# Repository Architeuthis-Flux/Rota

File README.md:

# Rǒta
Here are some different Rǒtas with different options

That flashing means it wants your input. These decimal points do way more work than regular decimal points, they tell you a lot about what's going on. When you don't have segments to make crude letters and stuff, you need to get creative with dots.

https://user-images.githubusercontent.com/20519442/197625332-2014cbfb-5107-4166-b01f-a8d20bc4a214.mp4

Rǒta is a tool for counting things while being all nerdily extra about it. Are there more efficient ways to count things? Yes. But will those things increase your exposure to Nixie tubes and rotary dials? No? Well then if that's what passes for progress nowadays then I'm going to go live on a mountain somewhere and count things the cooler way, with nixie tubes.

It was originally conceived as a gift for a duck hunting lodge, but now I'm making a few more and I know not everyone is into hunting so it's been generalized into a tool for just counting stuff in general where those $3 hand clickers or a golf pencil just lacks the glamour you need in your life. 

Instead of using sequences of numbers to use the special functions, now you just dial 0 and then the function you want which is printed on the number plate. 

here's the special function menu map
```
note - I'm calling moving the dial just a little to turn the display on a "click"
when inside a special function, dial anything to exit (preferably 0 because it's only reading intermittently when in menus, so it's most likely to register)

0 -- enter/exit menu or function   shows 111 when you're in the menu)
1 -- stopwatch                    click to start, click again to see last time.
2 -- show battery voltage         briefly turns off the display to get a more accurate reading (not under load)
3 -- new day                      this stores the total since the last time you started a new day. maximum 63 days
4 -- does nothing
5 -- enter a count by digits      enter 3 digits (hundreds - tens - ones) to add to your daily total
6 -- show history                 click through each day with first the day number (on the left) then the total for that day
7 -- toggle day/total display     either shows the count for that day or the running total of all days (default is total)
8 -- golf mode                    keep score for golf - first enter 1-4 players and the decimal points show which player's turn it is
9 -- clear everything             dial 9 again to confirm. dial anything else to go back
999999 -- emergency clear         dial 9 six times to emergency clear everything in case something gets messed up same as dialing 10 9 9
                                  you can also short the middle pulse pin high for super duper emergency clear

```

The voltage display was added because I was having issues with the K155ID1s browning out before the HV module (it still blows my mind that it works down to like 3V), so the display would just show all the digits on because the nixie drivers weren't blocking any current. 

So now I added a HV shutdown and a super simple voltage sense divider that drops the 9 down by half so it can be read by the AVR64DD32's ADC.

Now if the battery voltage is too low, it shuts down the display but still takes input. In case you don't have a spare battery but still want to count. And the power draw is so low for just the microcontroller that the battery life might as well be infinite.

https://user-images.githubusercontent.com/20519442/197626419-59003e0c-a97b-495f-a466-c8ea541df162.mp4

If you notice in the video, the display flashes when the battery voltage updates, that's because when it does the measurement, it briefly shuts the HV module down so we can measure the battery voltage unloaded. Because this thing draws ~300-400mA when it's on so without doing a ton of math and testing different 9v batteries to correct for it, the voltage it shows would be like ~2V lower than it really is unloaded. 

I probably should have put in a fresher battery before I filmed this. 

I also had to design a case for this because I'd always get anxious watching other people use it without one. People with smaller hands tend to put their fingers right on the high voltage section on the back of the Nixies. 

This project really helped me change my lukewarm feelings towards rapid prototyping, I've had a 3D printer for years but never really used it much. I found out the reason it never worked is the original spool of filament Sindoh included was garbage. So my prints would always turn into an absolute mess of spaghetti. I finally bought a fresh spool of filament and it works great now.

I'll definitely have the case made by someone with a more expensive printer when I sell these or give them away, but to get the fit right and make sure there's room for everything inside, 3D printing really saved the day here.

Putting in the number plate (which I just found out the name of) on these old dials really makes you appreciate how much thought they put into things in the 60's. Like on most phones you would only do this once, but they came up with a really cool system for it.

How you do it is by sticking a screwdriver under the ring at the 6 and moving a lever down to the 8 position to release the middle thing.

With it off you can see what's going on 

Then you just twist this pressure plate and it comes off. 

This isn't the final number plate from above because I'm a millennial and don't have a regular 2D printer. But I might try it on a plotter or a silkscreen to get a nicer finish.

I had to move the holes a bit to get it to line up with the dial, I must have carelessly moved the holes on the Edge Cuts layer in Kicad, but the new Kicad files on here are fixed (as well as a couple other problems) if you want to have these boards made yourself. 

Yes I cleaned that flux off. For Nixies it's particularly important because flux lets enough current flow at that voltage to cause ghosting. I had a lot of problems wit ghosting on the first digit and I tried a bunch of things to get rid of it, eventually what fixed it for me was putting a 220KΩ resistor between high voltage and ground to both drop the voltage a bit (these tiny HV modules don't have an adjustment knob like the bigger ones) and bleed off the extra charge you get when you do low-side switching on nixies.

PCBway was nice enough to sponsor this project. I had never used them before but the boards they sent were great. And their matte black finish is really velvety. 

It really seems like they spend a good deal of time with a human looking at your boards and making sure there aren't any problems. And I usually do a lot of weird stuff with my boards that falls outside of the usual best practices of PCB design. But they seemed to roll with it pretty well and make sure I did it on purpose (that came up a lot more with breadWare which they also sponsored.) Which is crazy to me because of how cheap the service is. You'd think it wouldn't be worth their time for my ~$20. 

Either way, I was ready to just pay them for my boards if they were shitty and say so here. But that wasn't necessary because they really did a great job on these. 

# RotaDuck (this is the previous revision so I'm leaving this here)
Sticking Nixie tubes to an old rotary telephone dial

Here's a video of it in action

https://user-images.githubusercontent.com/20519442/176002505-34b7ac66-cf38-471d-8984-42ffa85f04d7.mp4

And there's a few more on my [Youtube channel](https://www.youtube.com/user/arabidsquid/videos)

I'll do a more complete write-up at some point in the future, but for now I'll mention a few things.

It stores the running count (and a history of recent entries) in EEPROM because when the dial returns to it's resting position, the power is completely cut off. That makes it so I couldn't just use timing to figure out when the pulses stop (and the number that was ultimately dialed) so instead I put in a resistor ladder so the between the 3 contacts on the dial to give me 1/2 voltage on the last number, when the dial is between 0 and the end. that gives me a waveform like this:
```
   _   _   _   _
__| |_| |_| |_| |_,-,___
```
So it does all the saving during that shorter last pulse, which is pretty tight because EEPROM access is relatively slow. 

I didn't want to add any buttons to it so instead it uses multiple 9s and 0s for special codes, here's the list of what they do
```
0   - subtract the next number dialed from the total
000 - clear all counts to 0

9   - show total for all days
99  - list each day and the total for each
999 - start a new day
```
Here's what I'm talking about when I say days. So this was originally designed for duck hunting (hence the duck in the name) as a gift for a duck hunting club. If you want to count how many ducks you got, we'd usually bring one of those mechanical clicker counters and just keep a running total.But I figured if I'm making a thing to count how many ducks were shot during a trip, it might also be useful to have that information separated by days if you want to keep a separate daily and running total. 

At some point I'll print that menu in the middle of the dial.

If you intend to make one of these for yourself, you should probably know this thing is like 90% bodges and perfboard circuits. I eyeballed the shape of the dial cutout nearly perfect, except that it's flipped on the board. So instead of just redoing the board like a sane person, I just mounted it with everything on the wrong side and bodged wired a ton of things to make it work. That's why there are those arrays in the code to convert the number shown to the number its actually wired to. So if you really want one, let me know and I can do a version 2 that will be 100x easier to put together. 

I also made a rechargeable one by dead bug soldering a tiny 10DFN MCP73213T charge controller and putting in 2 1/2 AA sized lithium batteries, but after using it a while, the simplicity of just using a 9 volt battery is much nicer (and lasts a lot longer.)

Eventually that red wire sticking out will be connected to a barrel jack port. Once I decide on an enclosure.

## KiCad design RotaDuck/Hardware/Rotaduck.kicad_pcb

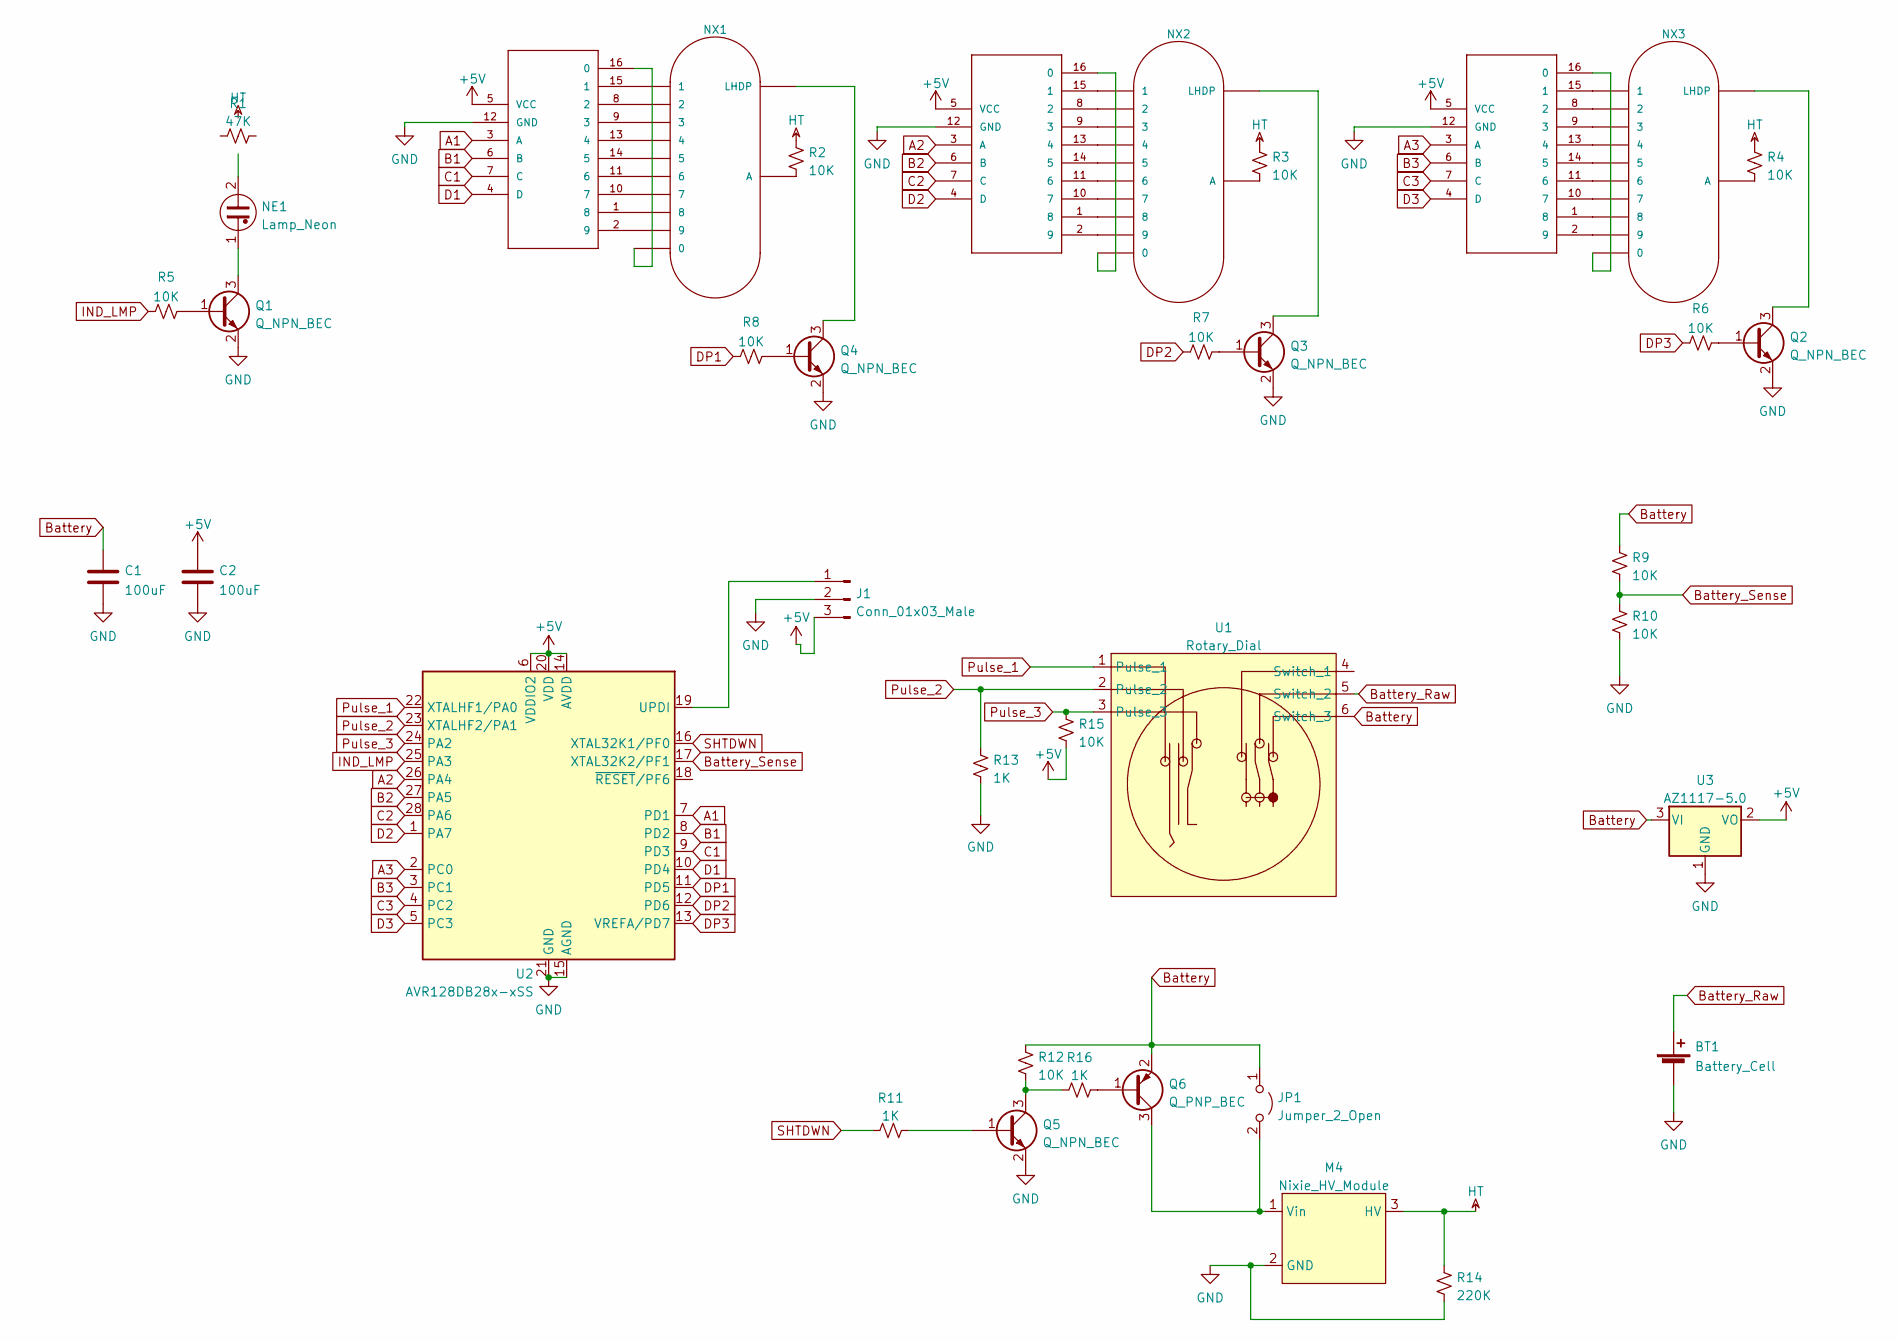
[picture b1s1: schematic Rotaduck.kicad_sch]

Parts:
BT1: Battery_Cell; PinHeader_1x02_P2.54mm_Vertical
C1, C2: 100uF; C_1206_3216Metric_Pad1.33x1.80mm_HandSolder
J1: Conn_01x03_Male; PinHeader_1x03_P2.54mm_Vertical
JP1: Jumper_2_Open; SolderJumper-2_P1.3mm_Open_RoundedPad1.0x1.5mm
M1, M2, M3: 74141DIP16; DIP-16_W7.62mm
M4: Nixie_HV_Module; Nixie_HV_Module_Small
NE1: Lamp_Neon; PinHeader_1x02_P2.54mm_Vertical
NX1, NX2, NX3: IN-12BNOHOLE; nixies-us-IN-12-DSUB
Q1, Q2, Q3, Q4, Q5: Q_NPN_BEC; SOT-23
Q6: Q_PNP_BEC; SOT-23
R1: 47K; R_1206_3216Metric_Pad1.30x1.75mm_HandSolder
R2, R3, R4: 10K; R_1206_3216Metric_Pad1.30x1.75mm_HandSolder
R5, R6, R7, R8, R9, R10, R12, R15: 10K; R_0805_2012Metric_Pad1.20x1.40mm_HandSolder
R11, R13, R16: 1K; R_0805_2012Metric_Pad1.20x1.40mm_HandSolder
R14: 220K; R_1206_3216Metric_Pad1.30x1.75mm_HandSolder
U1: Rotary_Dial; PinHeader_1x06_P2.54mm_Vertical
U2: AVR128DB28x-xSS; SSOP-28_5.3x10.2mm_P0.65mm
U3: AZ1117-5.0; SOT-223-3_TabPin2

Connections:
+5V: C2.1, J1.3, M1.5 (VCC), M2.5 (VCC), M3.5 (VCC), R15.2, U2.6 (VDDIO2), U2.14 (AVDD), U2.18 (~RESET/PF6), U2.20 (VDD), U3.2 (VO)
A1: M1.3 (A), U2.7 (PD1)
A2: M2.3 (A), U2.26 (PA4)
A3: M3.3 (A), U2.2 (PC0)
B1: M1.6 (B), U2.8 (PD2)
B2: M2.6 (B), U2.27 (PA5)
B3: M3.6 (B), U2.3 (PC1)
Battery: C1.1, JP1.1 (A), Q6.2 (E), R9.2, R12.1, U1.6 (Switch_3), U3.3 (VI)
Battery_Raw: BT1.1 (+), U1.5 (Switch_2)
Battery_Sense: R9.1, R10.2, U2.17 (XTAL32K2/PF1)
C1: M1.7 (C), U2.9 (PD3)
C2: M2.7 (C), U2.28 (PA6)
C3: M3.7 (C), U2.4 (PC2)
D1: M1.4 (D), U2.10 (PD4)
D2: M2.4 (D), U2.1 (PA7)
D3: M3.4 (D), U2.5 (PC3)
DP1: R8.2, U2.11 (PD5)
DP2: R7.2, U2.12 (PD6)
DP3: R6.2, U2.13 (VREFA/PD7)
GND: BT1.2 (-), C1.2, C2.2, J1.2, M1.12 (GND), M2.12 (GND), M3.12 (GND), M4.2 (GND), Q1.2 (E), Q2.2 (E), Q3.2 (E), Q4.2 (E), Q5.2 (E), R10.1, R13.2, R14.2, U2.15 (AGND), U2.21 (GND), U3.1 (GND)
HT: M4.3 (HV), R1.2, R2.2, R3.2, R4.2, R14.1
IND_LMP: R5.2, U2.25 (PA3)
unnamed: J1.1, U2.19 (UPDI)
unnamed: JP1.2 (B), M4.1 (Vin), Q6.3 (C)
unnamed: M1.1 (8), NX1.8
unnamed: M1.2 (9), NX1.9
unnamed: M1.8 (2), NX1.2
unnamed: M1.9 (3), NX1.3
unnamed: M1.10 (7), NX1.7
unnamed: M1.11 (6), NX1.6
unnamed: M1.13 (4), NX1.4
unnamed: M1.14 (5), NX1.5
unnamed: M1.15 (1), NX1.1
unnamed: M1.16 (0), NX1.0
unnamed: M2.1 (8), NX2.8
unnamed: M2.2 (9), NX2.9
unnamed: M2.8 (2), NX2.2
unnamed: M2.9 (3), NX2.3
unnamed: M2.10 (7), NX2.7
unnamed: M2.11 (6), NX2.6
unnamed: M2.13 (4), NX2.4
unnamed: M2.14 (5), NX2.5
unnamed: M2.15 (1), NX2.1
unnamed: M2.16 (0), NX2.0
unnamed: M3.1 (8), NX3.8
unnamed: M3.2 (9), NX3.9
unnamed: M3.8 (2), NX3.2
unnamed: M3.9 (3), NX3.3
unnamed: M3.10 (7), NX3.7
unnamed: M3.11 (6), NX3.6
unnamed: M3.13 (4), NX3.4
unnamed: M3.14 (5), NX3.5
unnamed: M3.15 (1), NX3.1
unnamed: M3.16 (0), NX3.0
unnamed: NE1.1, Q1.3 (C)
unnamed: NE1.2, R1.1
unnamed: NX1.A, R2.1
unnamed: NX1.LHDP, Q4.3 (C)
unnamed: NX2.A, R3.1
unnamed: NX2.LHDP, Q3.3 (C)
unnamed: NX3.A, R4.1
unnamed: NX3.LHDP, Q2.3 (C)
unnamed: Q1.1 (B), R5.1
unnamed: Q2.1 (B), R6.1
unnamed: Q3.1 (B), R7.1
unnamed: Q4.1 (B), R8.1
unnamed: Q5.3 (C), R12.2, R16.1
unnamed: Q5.1 (B), R11.1
unnamed: Q6.1 (B), R16.2
Pulse_1: U1.1 (Pulse_1), U2.22 (XTALHF1/PA0)
Pulse_2: R13.1, U1.2 (Pulse_2), U2.23 (XTALHF2/PA1)
Pulse_3: R15.1, U1.3 (Pulse_3), U2.24 (PA2)
SHTDWN: R11.2, U2.16 (XTAL32K1/PF0)

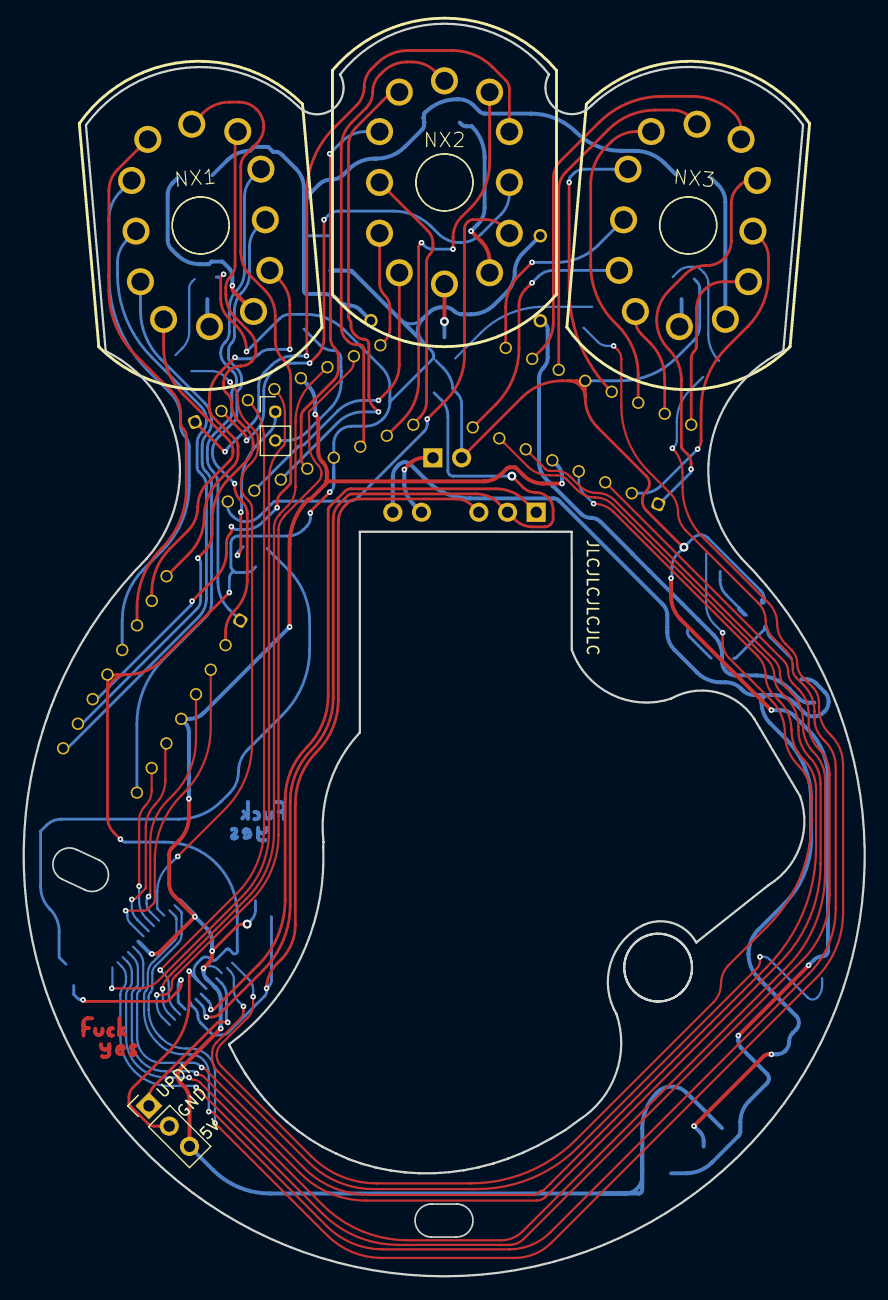
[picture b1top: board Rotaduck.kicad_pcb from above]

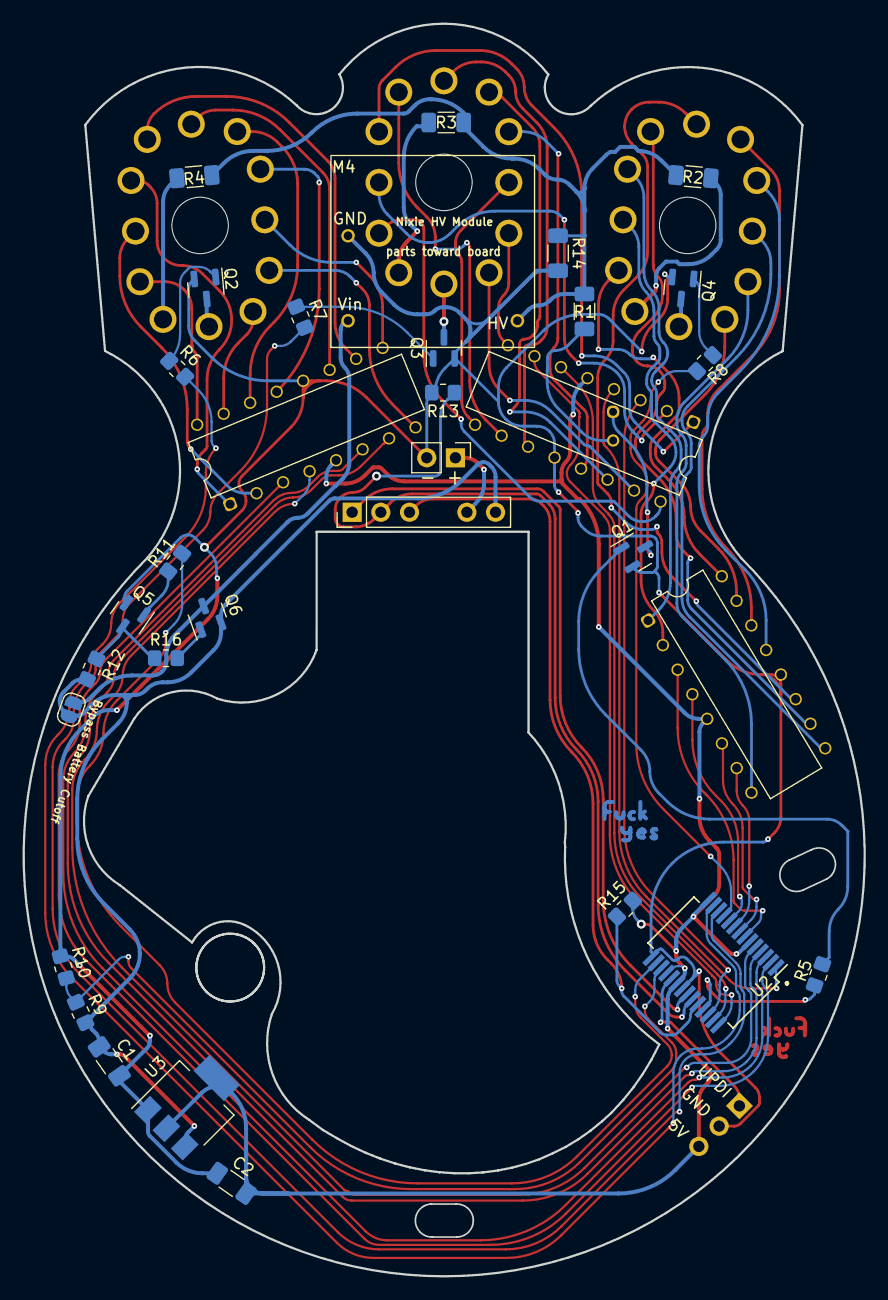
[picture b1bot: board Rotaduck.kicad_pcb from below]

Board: 2 copper layers, 74.5 x 110.9 mm, 38 parts (33 on the bottom side), 73 nets.

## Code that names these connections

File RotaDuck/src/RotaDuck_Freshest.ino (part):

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#define SUBFLAG 0x05
#define CLEARFLAG 0x06

#define dp0 PIN_PD5
#define dp1 PIN_PD6
#define dp2 PIN_PD7
#define ind PIN_PA3

#define pulse1 PIN_PA0
#define pulse2 PIN_PA1
#define pulse3 PIN_PA2

#define MEMLEN 64

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  splitBCD(-1);      //-1 shows nothing
  EEPROM.read(0x0D); // check for first startup (but this read gets thrown away because EEPROM can be weird)

  pinMode(PIN_PF0, OUTPUT); // this enables power to the HV supply
  digitalWriteFast(PIN_PF0, HIGH);

  pinMode(PIN_PD5, OUTPUT);
  pinMode(PIN_PD6, OUTPUT);
  pinMode(PIN_PD7, OUTPUT);
  digitalWriteFast(PIN_PD5, LOW);
  digitalWriteFast(PIN_PD6, LOW);
  digitalWriteFast(PIN_PD7, LOW);

  pinMode(PIN_PA4, OUTPUT);
  pinMode(PIN_PA5, OUTPUT);
  pinMode(PIN_PA6, OUTPUT);
  pinMode(PIN_PA7, OUTPUT);

  pinMode(pulse1, INPUT_PULLUP);
  pinMode(pulse2, INPUT);
  pinMode(pulse3, INPUT);
  pinMode(PIN_PA2, INPUT);

  pinMode(PIN_PA3, OUTPUT);

  pinMode(PIN_PD1, OUTPUT);
  pinMode(PIN_PD2, OUTPUT);
  pinMode(PIN_PD3, OUTPUT);
  pinMode(PIN_PD4, OUTPUT);

  pinMode(PIN_PF1, INPUT);

  pinMode(PIN_PC0, OUTPUT);
  pinMode(PIN_PC1, OUTPUT);
  pinMode(PIN_PC2, OUTPUT);
  pinMode(PIN_PC3, OUTPUT);

  analogReadResolution(10);
  analogSampleDuration(500);
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void dispNix(void)
{

  digitalWriteFast(PIN_PC0, truthBCD[dispDig0][3]);
  digitalWriteFast(PIN_PC1, truthBCD[dispDig0][2]);
  digitalWriteFast(PIN_PC2, truthBCD[dispDig0][1]);
  digitalWriteFast(PIN_PC3, truthBCD[dispDig0][0]);

  digitalWriteFast(PIN_PA4, truthBCD[dispDig1][3]);
  digitalWriteFast(PIN_PA5, truthBCD[dispDig1][2]);
  digitalWriteFast(PIN_PA6, truthBCD[dispDig1][1]);
  digitalWriteFast(PIN_PA7, truthBCD[dispDig1][0]);

  digitalWriteFast(PIN_PD1, truthBCD[dispDig2][3]);
  digitalWriteFast(PIN_PD2, truthBCD[dispDig2][2]);
  digitalWriteFast(PIN_PD3, truthBCD[dispDig2][1]);
  digitalWriteFast(PIN_PD4, truthBCD[dispDig2][0]);
}

void splitBCD(int dispNum)
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
    if (loaded > 0)
    {
      digitalWriteFast(PIN_PF0, LOW);
      delay(loaded); // let battery voltage bounce back up a bit
    }
    total = 0;
    for (int i = 0; i < numSamps; i++)
    {
      total += analogRead(PIN_PF1);
      delayMicroseconds(loaded * 2);
    }

    digitalWriteFast(PIN_PF0, HIGH);

    int voltage = (total / numSamps);
    splitBCD(voltage + 11);
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
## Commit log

2022-08-14 Rewrote most of the code for new hardware
    Changed the menu system and added:
    -golf scoring mode
    -stopwatch
    -voltage readout
    -digit-wise entry
2022-11-14 Create p
2022-11-15 Create d
2022-11-15 Rename Rota_Assembly_Instructions.md to README.md
2022-12-11 Create LICENSE
2022-12-11 Update LICENSE
